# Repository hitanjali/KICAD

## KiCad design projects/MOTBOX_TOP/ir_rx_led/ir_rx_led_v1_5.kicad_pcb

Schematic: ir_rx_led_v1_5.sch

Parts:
D1, D2: PD333-3B/H0/L2; LED_D5.0mm_Horizontal_O6.35mm_Z9.0mm
H1, H2, H3, H4: MountingHole; MountingHole_3.2mm_M3_DIN965
H5, H6, H7: MountingHole; MountingHole_2.2mm_M2_DIN965
J1: Conn_01x03; SolderWirePad_1x03_P3.175mm_Drill0.8mm

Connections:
unnamed: D1.1 (K), J1.2
unnamed: D1.2 (A), D2.2 (A), J1.1
unnamed: D2.1 (K), J1.3

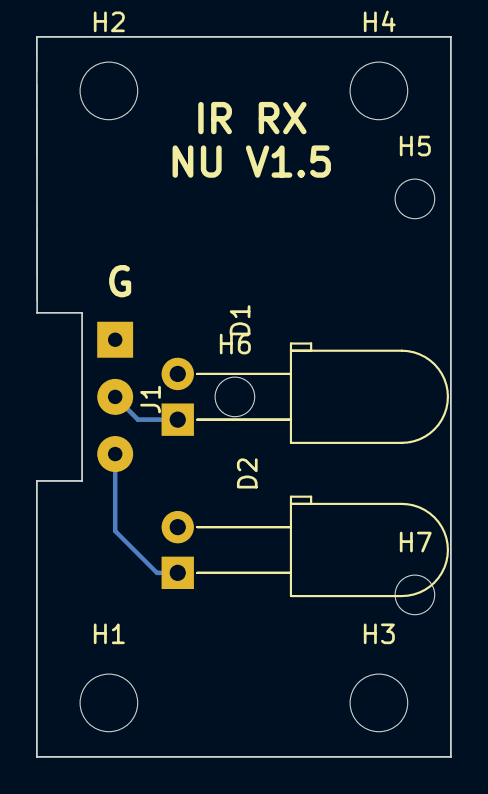
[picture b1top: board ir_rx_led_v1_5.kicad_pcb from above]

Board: 2 copper layers, 23.0 x 40.0 mm, 10 parts (0 on the bottom side), 3 nets.

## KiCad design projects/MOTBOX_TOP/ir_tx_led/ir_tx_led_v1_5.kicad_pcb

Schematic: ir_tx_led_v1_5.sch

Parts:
D1, D2: IR333-A; LED_D5.0mm_Horizontal_O6.35mm_Z9.0mm
H1, H2, H3, H4: MountingHole; MountingHole_3.2mm_M3_DIN965
H5, H6, H7: MountingHole; MountingHole_2.2mm_M2_DIN965
J1: Conn_01x03; SolderWirePad_1x03_P3.175mm_Drill0.8mm

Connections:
unnamed: D1.1 (K), D2.1 (K), J1.1
unnamed: D1.2 (A), J1.3
unnamed: D2.2 (A), J1.2

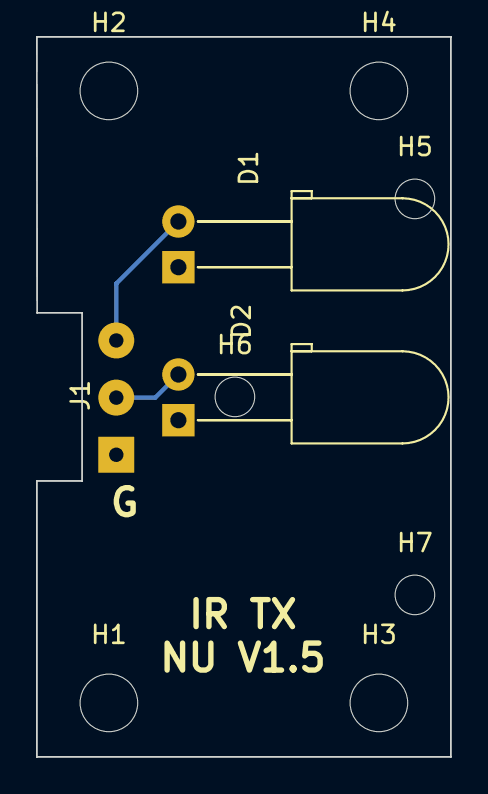
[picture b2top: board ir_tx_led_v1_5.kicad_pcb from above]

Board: 2 copper layers, 23.0 x 40.0 mm, 10 parts (0 on the bottom side), 3 nets.

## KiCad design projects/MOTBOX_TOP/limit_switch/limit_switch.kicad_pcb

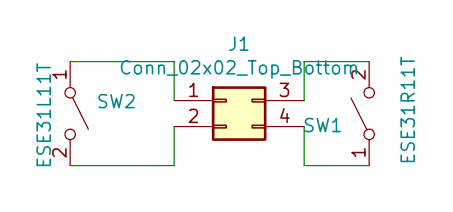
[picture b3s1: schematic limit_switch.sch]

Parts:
J1: Conn_02x02_Top_Bottom; SolderWirePad_2x02_P2.54mm_Drill0.8mm
SW1: ESE31R11T; ESE58R11T_Detector_SW_2pin_right
SW2: ESE31L11T; ESE58L11T_Detector_SW_2pin_left

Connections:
unnamed: J1.1, SW2.1 (A)
unnamed: J1.2, SW2.2 (B)
unnamed: J1.3, SW1.2 (B)
unnamed: J1.4, SW1.1 (A)

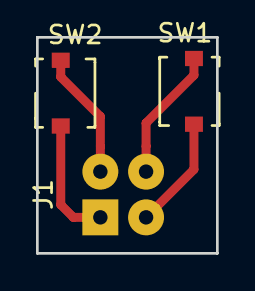
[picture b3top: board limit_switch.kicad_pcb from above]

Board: 2 copper layers, 10.0 x 12.0 mm, 3 parts (0 on the bottom side), 4 nets.

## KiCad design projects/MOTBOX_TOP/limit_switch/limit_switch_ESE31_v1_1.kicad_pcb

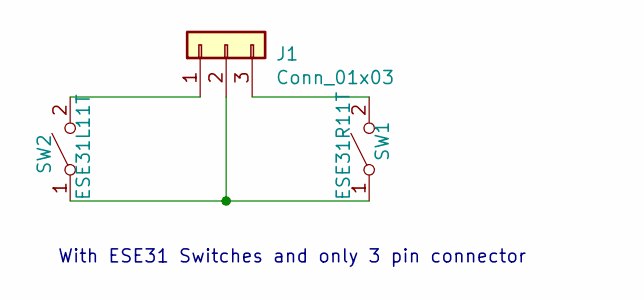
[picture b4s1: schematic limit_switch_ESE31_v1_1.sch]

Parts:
J1: Conn_01x03; SolderWirePad_1x03_P3.175mm_Drill0.8mm
SW1: ESE31R11T; ESE31R11T_Detector_SW_2pin_right
SW2: ESE31L11T; ESE31L11T_Detector_SW_2pin_left

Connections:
unnamed: J1.1, SW2.2 (B)
unnamed: J1.2, SW1.1 (A), SW2.1 (A)
unnamed: J1.3, SW1.2 (B)

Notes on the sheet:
With ESE31 Switches and only 3 pin connector

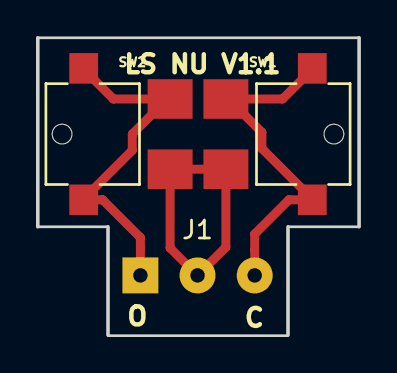
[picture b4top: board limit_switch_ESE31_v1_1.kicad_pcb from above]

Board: 2 copper layers, 17.8 x 16.5 mm, 3 parts (0 on the bottom side), 3 nets.

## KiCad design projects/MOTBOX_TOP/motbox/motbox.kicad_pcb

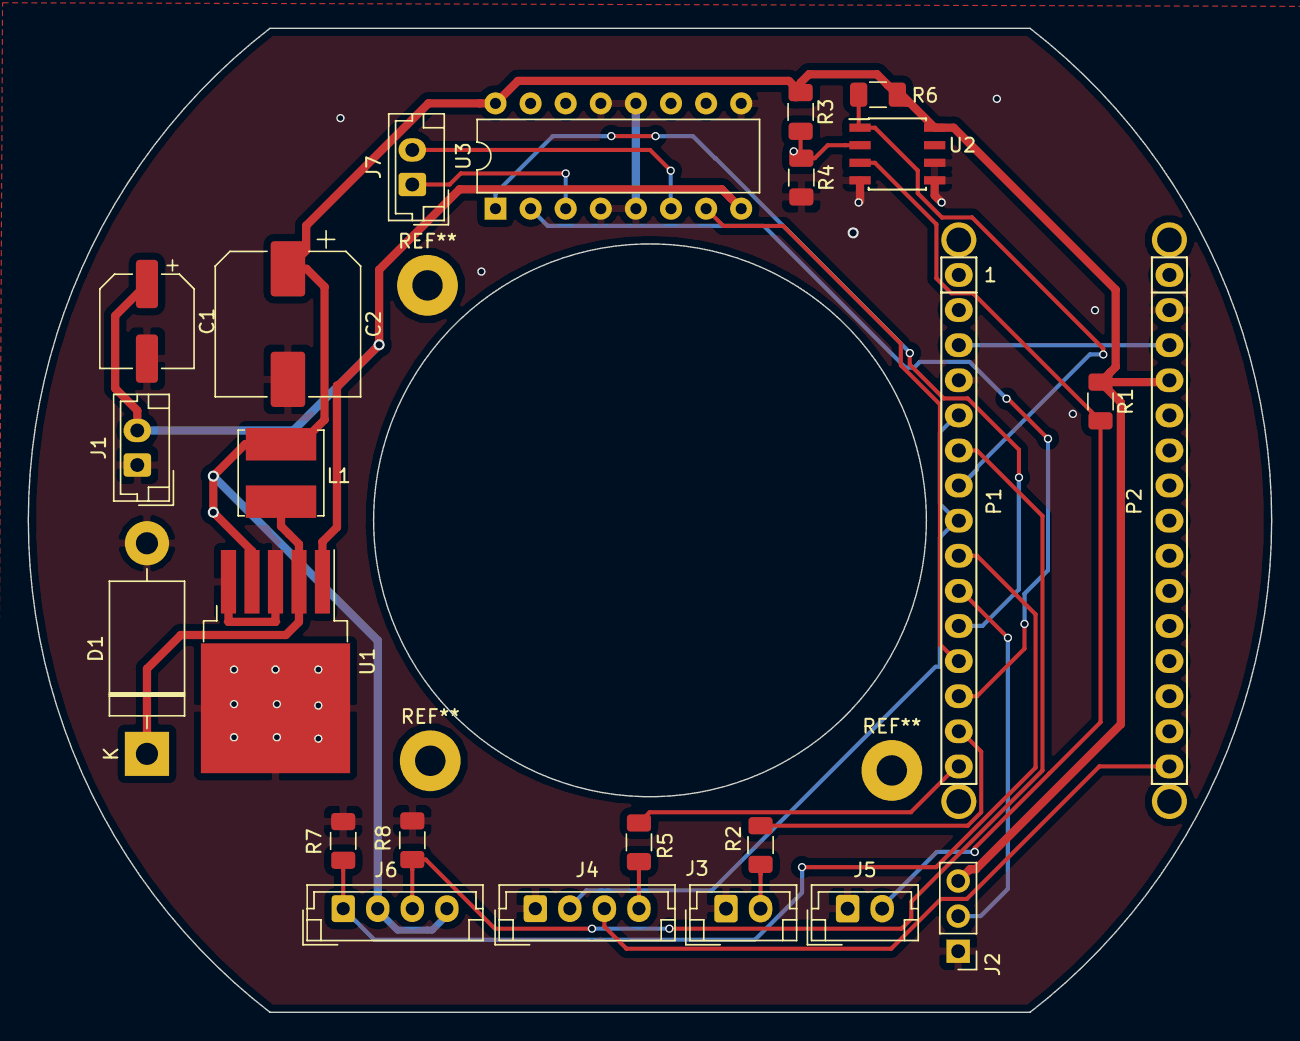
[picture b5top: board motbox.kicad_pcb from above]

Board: 2 copper layers, 90.0 x 71.2 mm, 28 parts (0 on the bottom side), 22 nets.

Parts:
C1: 100uF; CP_Elec_6.3x7.7
C2: 1000uF; CP_Elec_10x10
D1: 1N5822; D_DO-201AD_P15.24mm_Horizontal
J1: 12V IN; JST_EH_B02B-EH-A_1x02_P2.50mm_Vertical
J2: Manual EN; PinHeader_1x03_P2.54mm_Vertical
J3: OBS_IR_TX; JST_EH_B02B-EH-A_1x02_P2.50mm_Vertical
J4: OP_CL_OBS_DET_LED; JST_EH_B04B-EH-A_1x04_P2.50mm_Vertical
J5: OBS IR RX; JST_EH_B02B-EH-A_1x02_P2.50mm_Vertical
J6: Open Close Done; JST_EH_B04B-EH-A_1x04_P2.50mm_Vertical
J7: Motor; JST_EH_B02B-EH-A_1x02_P2.50mm_Vertical
L1: 100UH; L_Bourns_SRN6045TA
P1: Digital; Socket_Strip_Arduino_1x15
P2: Analog; Socket_Strip_Arduino_1x15
P3, P4, P5, P6: CONN_01X01; 1pin_Nano
R1: TBD; R_1206_3216Metric
R2, R5: 150; R_1206_3216Metric
R3, R4, R7, R8: 100K; R_1206_3216Metric
R6: 10K; R_1206_3216Metric
U1: LM2575-5.0BU; TO-263-5_TabPin3
U2: LM393; SOIC-8_3.9x4.9mm_P1.27mm
U3: L293D; DIP-16_W7.62mm

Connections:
+5V: C2.1, J2.3, J6.2, J6.4, L1.2, P2.4, R1.1, R3.1, R6.1, U1.4, U2.8, U3.16
+12V: C1.1, J1.2, U1.1, U3.8
/2: J4.2, P1.5, P1.8
/3: J6.3, P1.6, R8.1
/4: P1.7, R6.2, U2.1
/6: J6.1, P1.9, R7.1
/7: J2.2, P1.10
/8: P1.11, U3.1
/9: P1.12, U3.7
/10: P1.13, U3.2
/11: P1.14, R2.1
/12: P1.15, R5.1
/13: J4.3, P2.15
/Reset: P1.3, P2.3
GND: C1.2, C2.2, D1.2, J1.1, J2.1, J3.1, J4.1, J5.1, P1.4, P2.2, R4.2, R7.2, R8.2, U1.3, U1.5, U2.4, U2.5, U2.6, U3.4, U3.5, U3.9, U3.12, U3.13
unnamed: D1.1, L1.1, U1.2
unnamed: J3.2, R2.2
unnamed: J4.4, R5.2
unnamed: J5.2, R1.2, U2.3
unnamed: J7.1, U3.3
unnamed: J7.2, U3.6
unnamed: R3.2, R4.1, U2.2

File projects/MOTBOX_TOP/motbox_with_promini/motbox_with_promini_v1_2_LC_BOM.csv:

S.No,Manufacturing Part No,Designator,Quantity,Description(VALUE),Package(CASE),Top/Bottom,Points (No. of Pins),Comments,,
1,  , "C1, " , "1" , "100uF,25V" , "Capacitor_THT:CP_Radial_D6.3mm_P2.50mm" , TOP , 2, "Polarized capacitor, small US symbol", , 
2,  , "C2, " , "1" , "1000uF,16V" , "Capacitor_THT:CP_Radial_D10.0mm_P5.00mm" , TOP , 2, "Polarized capacitor, small US symbol", , 
3,  , "D1, " , "1" , "SS34" , "Diode_SMD:D_SMC" , TOP , 2, "Schottky diode", , 
4,  , "J2, " , "1" , "Header_3pin_Male" , "Connector_PinHeader_2.54mm:PinHeader_1x03_P2.54mm_Vertical" , TOP , 3, "Generic connector, single row, 01x03, script generated (kicad-library-utils/schlib/autogen/connector/)", , 
5,  , "J4, " , "1" , "JST_XH_4pin" , "Connector_JST:JST_XH_B04B-XH-A_1x04_P2.50mm_Vertical" , TOP , 4, "Generic connector, single row, 01x04, script generated (kicad-library-utils/schlib/autogen/connector/)", , 
6,  , "J5, J7, J1, J3, " , "4" , "JST_XH_2pin" , "Connector_JST:JST_XH_B02B-XH-A_1x02_P2.50mm_Vertical" , TOP , 2, "Generic connector, single row, 01x02, script generated (kicad-library-utils/schlib/autogen/connector/)", , 
7,  , "J6, " , "1" , "JST_XH_3pin" , "Connector_JST:JST_XH_B03B-XH-A_1x03_P2.50mm_Vertical" , TOP , 3, "Generic connector, single row, 01x03, script generated (kicad-library-utils/schlib/autogen/connector/)", , 
8,  , "L1, " , "1" , "SRN6045-101M" , "Inductor_SMD:L_Bourns_SRN6045TA" , TOP , 2, "Inductor, small symbol", , 
9,  , "P1, P5, " , "2" , "Female_Header_12pin" , "Socket_Arduino_Pro_Mini:Socket_Strip_Arduino_1x12" , TOP , 12, "Generic connector, single row, 01x12, script generated (kicad-library-utils/schlib/autogen/connector/)", , 
10,  , "P3, " , "1" , "Female_Header_6pin" , "Socket_Arduino_Pro_Mini:Socket_Strip_Arduino_1x06" , TOP , 6, "Generic connector, single row, 01x06, script generated (kicad-library-utils/schlib/autogen/connector/)", , 
11,  , "R1, " , "1" , "60K" , "Resistor_SMD:R_1206_3216Metric" , TOP , 2, "Resistor, US symbol", , 
12,  , "R2, R5, " , "2" , "150R" , "Resistor_SMD:R_1206_3216Metric" , TOP , 2, "Resistor, US symbol", , 
13,  , "R3, R4, R8, R7, " , "4" , "100K" , "Resistor_SMD:R_1206_3216Metric" , TOP , 2, "Resistor, US symbol", , 
14,  , "R6, " , "1" , "10K" , "Resistor_SMD:R_1206_3216Metric" , TOP , 2, "Resistor, US symbol", , 
15,  , "U1, " , "1" , "LM2576R-5.0" , "Package_TO_SOT_SMD:TO-263-5_TabPin3" , TOP , 5, "12V, 3A SIMPLE SWITCHER® Step-Down Voltage Regulator, High Voltage Input, TO-263", , 
16,  , "U2, " , "1" , "LM393" , "Package_SO:SOIC-8_3.9x4.9mm_P1.27mm" , TOP , 8, "Low-Power, Low-Offset Voltage, Dual Comparators, DIP-8/SOIC-8/SSOP-8", , 
17,  , "U3, " , "1" , "L293D" , "Package_DIP:DIP-16_W7.62mm" , TOP , 16, "Quadruple Half-H Drivers", ,
